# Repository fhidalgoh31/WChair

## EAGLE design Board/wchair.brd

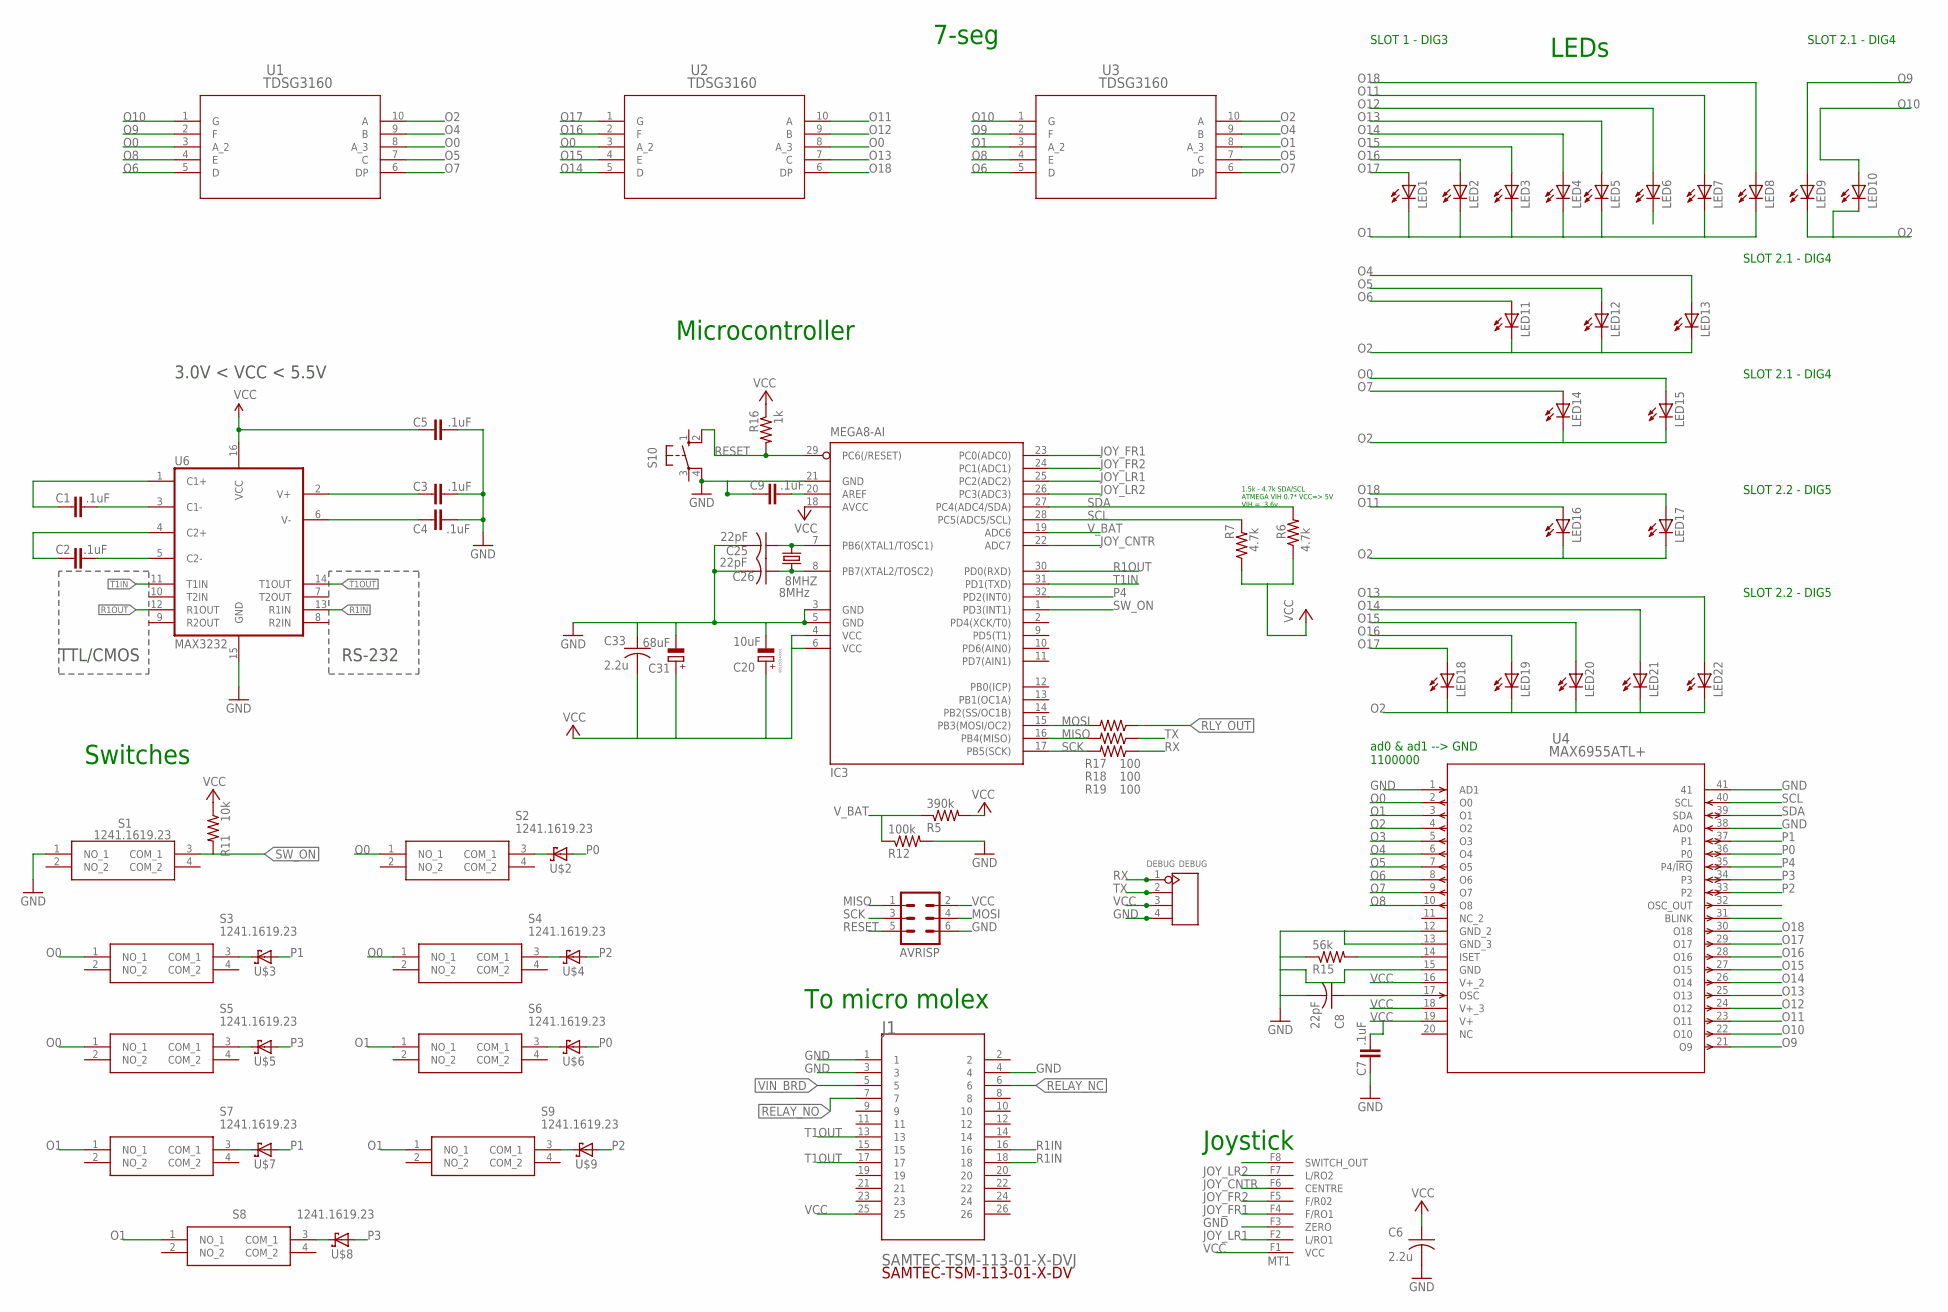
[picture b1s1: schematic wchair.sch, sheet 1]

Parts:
8MHZ: 8MHz; SM49; DIGIKEY 535-9089-1-ND
AVRISP: MA03-2; DIGIKEY ED10665-ND
C1, C2, C3, C4, C5, C7, C9: .1uF; 0603-CAP; DIGIKEY 399-15351-1-ND
C6, C33: 2.2u; C0603; DIGIKEY 1276-1183-1-ND
C8, C25, C26: 22pF; C0603; DIGIKEY 478-11384-1-ND
C20: 10uF; 153CLV-0405; DIGIKEY 493-2173-1-ND
C31: 68uF; 153CLV-0807; DIGIKEY PCE4412CT-ND‎
DEBUG: DEBUG; 4-PIN-HEADER; DIGIKEY 0
IC3: MEGA8-AI; TQFP32-08; DIGIKEY ATMEGA328P-AU-ND
J1: SAMTEC-TSM-113-01-X-DVJ; SAMTEC-TSM-113-01-X-DV
LED1, LED2, LED3, LED4, LED5, LED6, LED7, LED8, LED9, LED10, LED11, LED12, LED13, LED14, LED15, LED16, LED17, LED18, LED19, LED20, LED21, LED22: LEDCHIP-LED0805; CHIP-LED0805; DIGIKEY 1497-1434-1-ND
MT1: MINITEK2-8PINS
R5: 390k; R0603; DIGIKEY 311-390KGRCT-ND
R6, R7: 4.7k; R0603; DIGIKEY 311-4.7KGRCT-ND
R11: 10k; R0603; DIGIKEY RNCP0603FTD10K0CT-ND
R12: 100k; R0603; DIGIKEY RR08P100KDCT-ND
R15: 56k; R0603; DIGIKEY 749-1667-1-ND
R16: 1k; R0603; DIGIKEY RHM1.0KDCT-ND
R17, R18, R19: 100; R0603; DIGIKEY RR08P100DCT-ND
S1, S2, S3, S4, S5, S6, S7, S8, S9: 1241.1619.23; IP40-J-LEAD; DIGIKEY 486-1931-1-ND
S10: 10-XX; B3F-10XX; DIGIKEY SW400-ND
U1, U2, U3: TDSG3160; DIP10_TDS; DIGIKEY TDSG3160-M-ND
U4: MAX6955ATL+; 21-0141I_T4066-5
U6: MAX3232; SO16; DIGIKEY 296-14619-1-ND
U$2, U$3, U$4, U$5, U$6, U$7, U$8, U$9: SCHOTTKY; SOD-323

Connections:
C1+: C1.1, U6.1 (C1+)
C1-: C1.2, U6.3 (C1-)
C2+: C2.1, U6.4 (C2+)
C2-: C2.2, U6.5 (C2-)
GND: AVRISP.6, C3.2, C4.2, C5.2, C6.2, C7.1, C8.2, C9.1, C20.-, C25.2, C26.2, C31.-, C33.1, DEBUG.4, IC3.3 (GND), IC3.5 (GND), IC3.21 (GND), J1.1, J1.3, J1.4, MT1.F3 (ZERO), R12.2, R15.1, S1.1 (NO_1), S10.4 (P1), U4.1 (AD1), U4.12 (GND_2), U4.13 (GND_3), U4.15 (GND), U4.38 (AD0), U4.41, U6.15 (GND); also elsewhere on the board
JOY_CNTR: IC3.22 (ADC7), MT1.F6 (CENTRE)
JOY_FR1: IC3.23 (PC0(ADC0)), MT1.F4 (F/RO1)
JOY_FR2: IC3.24 (PC1(ADC1)), MT1.F5 (F/R02)
JOY_LR1: IC3.25 (PC2(ADC2)), MT1.F2 (L/RO1)
JOY_LR2: IC3.26 (PC3(ADC3)), MT1.F7 (L/RO2)
MISO: AVRISP.1, IC3.16 (PB4(MISO)), R18.2
MOSI: AVRISP.4, IC3.15 (PB3(MOSI/OC2)), R19.2
unnamed: S2.3 (COM_1), U$2.C
unnamed: S9.3 (COM_1), U$9.C
unnamed: S7.3 (COM_1), U$7.C
unnamed: S8.3 (COM_1), U$8.C
unnamed: S6.3 (COM_1), U$6.C
unnamed: S4.3 (COM_1), U$4.C
unnamed: S5.3 (COM_1), U$5.C
unnamed: S3.3 (COM_1), U$3.C
unnamed: R15.2, U4.14 (ISET)
unnamed: C8.1, U4.17 (OSC)
unnamed: 8MHZ.2, C25.1, IC3.7 (PB6(XTAL1/TOSC1))
unnamed: 8MHZ.1, C26.1, IC3.8 (PB7(XTAL2/TOSC2))
unnamed: C9.2, IC3.20 (AREF)
O0: LED15.A, S2.1 (NO_1), S3.1 (NO_1), S4.1 (NO_1), S5.1 (NO_1), U1.3 (A_2), U1.8 (A_3), U2.3 (A_2), U2.8 (A_3), U4.2 (O0)
O1: LED1.C, LED2.C, LED3.C, LED4.C, LED5.C, LED7.C, LED8.C, S6.1 (NO_1), S7.1 (NO_1), S8.1 (NO_1), S9.1 (NO_1), U3.3 (A_2), U3.8 (A_3), U4.3 (O1)
O2: LED9.C, LED10.C, LED11.C, LED12.C, LED13.C, LED14.C, LED15.C, LED16.C, LED17.C, LED18.C, LED19.C, LED20.C, LED21.C, LED22.C, U1.10 (A), U3.10 (A), U4.4 (O2)
O3: U4.5 (O3)
O4: LED13.A, U1.9 (B), U3.9 (B), U4.6 (O4)
O5: LED12.A, U1.7 (C), U3.7 (C), U4.7 (O5)
O6: LED11.A, U1.5 (D), U3.5 (D), U4.8 (O6)
O7: LED14.A, U1.6 (DP), U3.6 (DP), U4.9 (O7)
O8: U1.4 (E), U3.4 (E), U4.10 (O8)
O9: LED9.A, U1.2 (F), U3.2 (F), U4.21 (O9)
O10: LED10.A, U1.1 (G), U3.1 (G), U4.22 (O10)
O11: LED7.A, LED16.A, U2.10 (A), U4.23 (O11)
O12: LED6.A, U2.9 (B), U4.24 (O12)
O13: LED5.A, LED22.A, U2.7 (C), U4.25 (O13)
O14: LED4.A, LED21.A, U2.5 (D), U4.26 (O14)
O15: LED3.A, LED20.A, U2.4 (E), U4.27 (O15)
O16: LED2.A, LED19.A, U2.2 (F), U4.28 (O16)
O17: LED1.A, LED18.A, U2.1 (G), U4.29 (O17)
O18: LED8.A, LED17.A, U2.6 (DP), U4.30 (O18)
P0: U4.36 (P0), U$2.A, U$6.A
P1: U4.37 (P1), U$3.A, U$7.A
P2: U4.33 (P2), U$4.A, U$9.A
P3: U4.34 (P3), U$5.A, U$8.A
P4: IC3.32 (PD2(INT0)), U4.35 (P4/!IRQ)
R1IN: J1.16, J1.18, U6.13 (R1IN)
R1OUT: IC3.30 (PD0(RXD)), U6.12 (R1OUT)
RELAY_NC: J1.6; also elsewhere on the board
RELAY_NO: J1.7; also elsewhere on the board
RESET: AVRISP.5, IC3.29 (PC6(/RESET)), R16.2, S10.2 (S1)
RLY_OUT: R19.1; also elsewhere on the board
RX: DEBUG.1, R17.1
SCK: AVRISP.3, IC3.17 (PB5(SCK)), R17.2
SCL: IC3.28 (PC5(ADC5/SCL)), R7.2, U4.40 (SCL)
SDA: IC3.27 (PC4(ADC4/SDA)), R6.2, U4.39 (SDA)
SW_ON: IC3.1 (PD3(INT1)), R11.2, S1.3 (COM_1)
T1IN: IC3.31 (PD1(TXD)), U6.11 (T1IN)
T1OUT: J1.13, J1.17, U6.14 (T1OUT)
TX: DEBUG.2, R18.1
V+: C3.1, U6.2 (V+)
V-: C4.1, U6.6 (V-)
VCC: AVRISP.2, C5.1, C6.1, C7.2, C20.+, C31.+, C33.2, DEBUG.3, IC3.4 (VCC), IC3.6 (VCC), IC3.18 (AVCC), J1.25, MT1.F1 (VCC), R5.2, R6.1, R7.1, R11.1, R16.1, U4.16 (V+_2), U4.18 (V+_3), U4.19 (V+), U6.16 (VCC); also elsewhere on the board
VIN_BRD: J1.5; also elsewhere on the board
V_BAT: IC3.19 (ADC6), R5.1, R12.1

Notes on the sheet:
1.5k - 4.7k SDA/SCL ATMEGA VIH 0.7* VCC=> 5V VIH = 3.6v
Microcontroller
To micro molex
Joystick
Switches
7-seg
LEDs
RS-232
TTL/CMOS
3.0V < VCC < 5.5V
ad0 & ad1 --> GND 1100000
SLOT 1 - DIG3
SLOT 2.1 - DIG4
SLOT 2.2 - DIG5

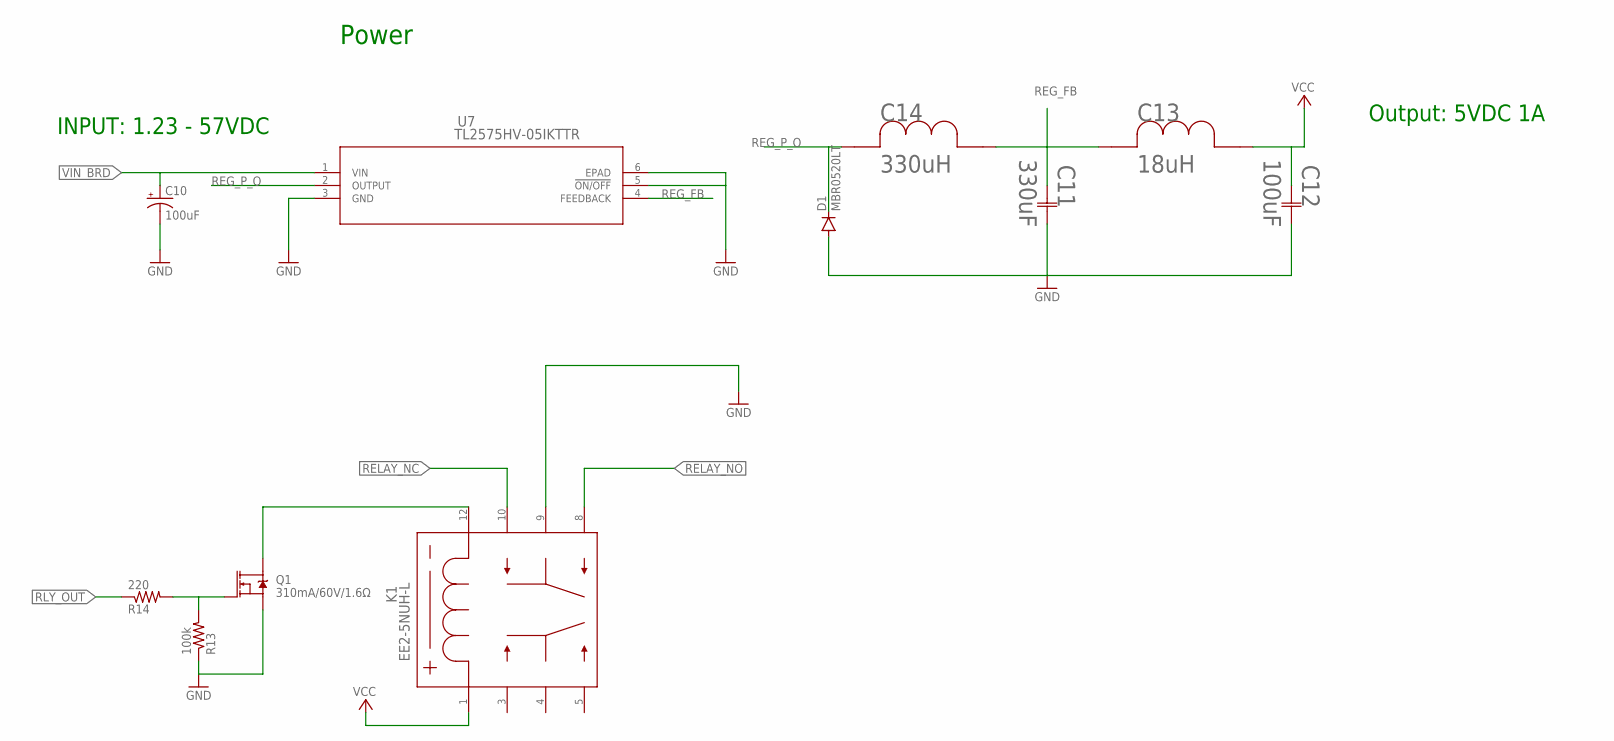
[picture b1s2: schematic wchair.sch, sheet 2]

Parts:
C10: 100uF; NIC_10X10.5_CAP; DIGIKEY PCE3942CT-ND
C11: 330uF; CAP_EEFK_D8; DIGIKEY PCE3768CT-ND
C12: 100uF; CAP_EEE_D; DIGIKEY PCE3852CT-ND
C13: 18uH; 18UH2.15A; DIGIKEY 732-4533-1-ND
C14: 330uH; 732-1698-1-ND; DIGIKEY 732-1698-1-ND
D1: MBR0520LT; SOD123; DIGIKEY MBR0520LCT-ND
K1: EE2-5NUH-L; EE2NUH; DIGIKEY 399-11016-1-ND‎
Q1: 310mA/60V/1.6Ω; SOT323; DIGIKEY SI2304BDS-T1-GE3CT-ND
R13: 100k; R0603; DIGIKEY RR08P100KDCT-ND
R14: 220; R0603; DIGIKEY A130087CT-ND
U7: TL2575HV-05IKTTR; KTT5_6P22X6P86; DIGIKEY 296-21833-1-ND

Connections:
GND: C10.-, C11.2, C12.2, D1.A, K1.9 (6), Q1.2 (S), R13.1, U7.3 (GND), U7.5 (!ON/OFF), U7.6 (EPAD); also elsewhere on the board
unnamed: Q1.1 (G), R13.2, R14.2
unnamed: K1.12 (8), Q1.3 (D)
REG_FB: C11.1, C13.1, C14.2, U7.4 (FEEDBACK)
REG_P_O: C14.1, D1.C, U7.2 (OUTPUT)
RELAY_NC: K1.10 (7); also elsewhere on the board
RELAY_NO: K1.8 (5); also elsewhere on the board
RLY_OUT: R14.1; also elsewhere on the board
VCC: C12.1, C13.2, K1.1; also elsewhere on the board
VIN_BRD: C10.+, U7.1 (VIN); also elsewhere on the board

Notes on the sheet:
Power
Output: 5VDC 1A
INPUT: 1.23 - 57VDC

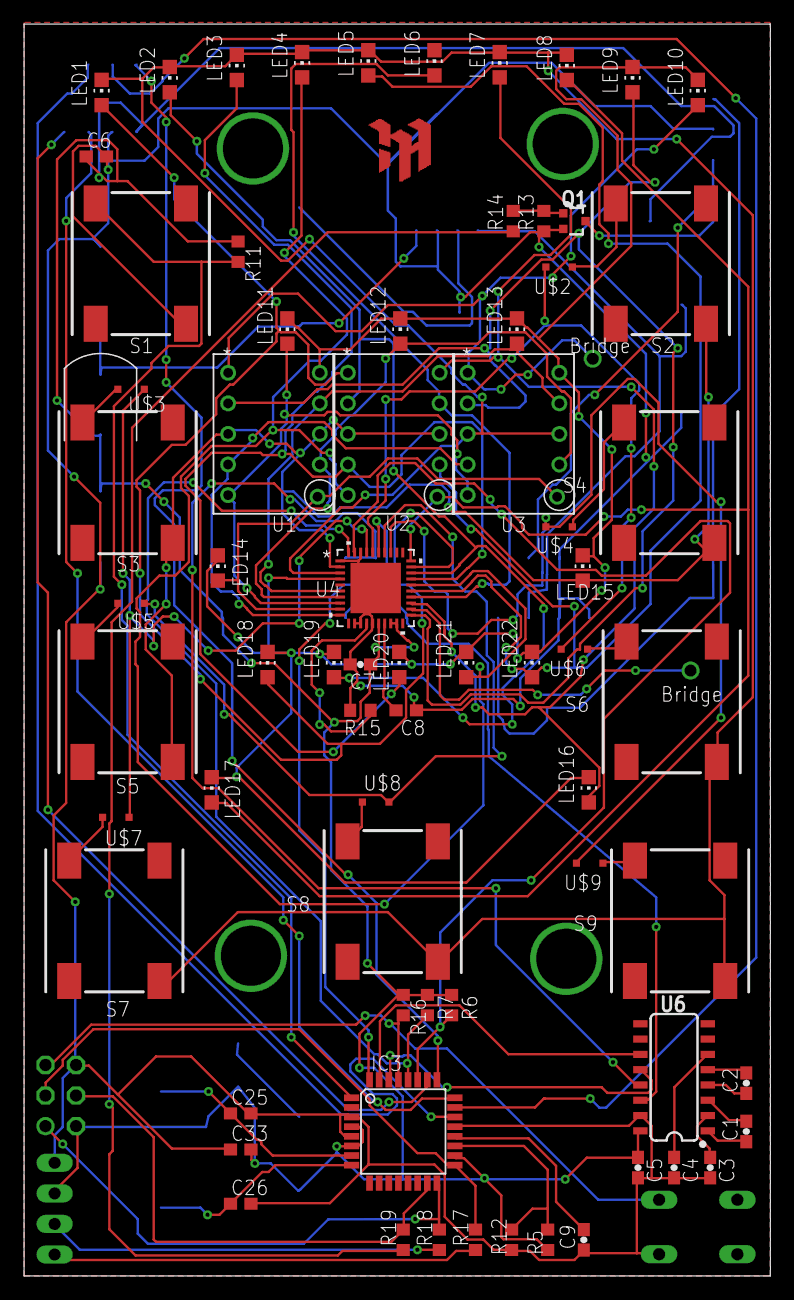
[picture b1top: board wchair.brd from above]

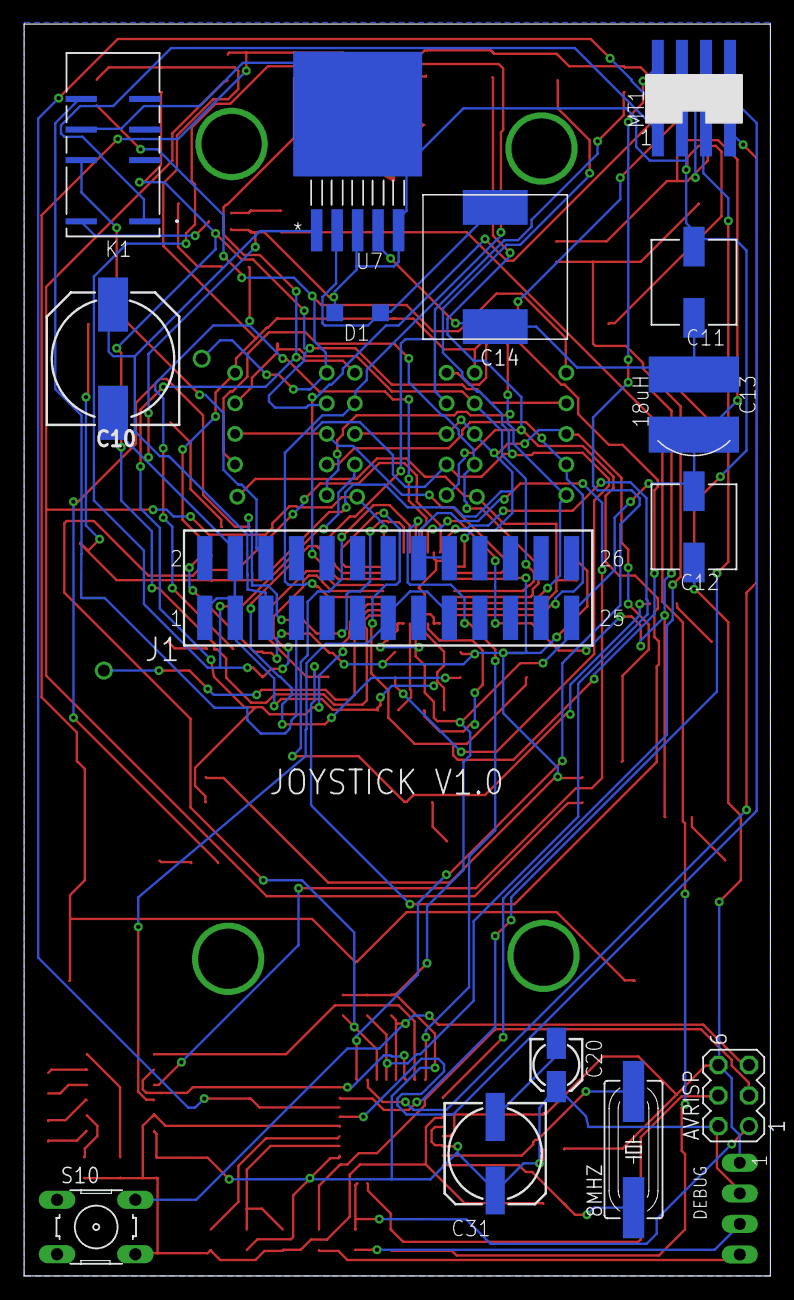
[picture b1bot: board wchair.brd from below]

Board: 2 copper layers, 62.0 x 104.0 mm, 86 parts (16 on the bottom side), 71 nets.

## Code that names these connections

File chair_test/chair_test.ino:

#include <SoftwareSerial.h>
#include <Wire.h>
#include "MAX6955.h"



#define JOY_FR1 A0
#define JOY_FR2 A1
#define JOY_LR1 A2
#define JOY_LR2 A3
#define JOY_CNTR A7

SoftwareSerial mySerial(13, 12); // RX, TX
MAX6955 leds(0B11000000);

void setup() {
  // set the data rate for the SoftwareSerial port
  Serial.begin(115200);
  mySerial.begin(115200);
 
  mySerial.println("Hello,  2??????");

 delay(10);
 leds.init();
 
}

void loop() { // run over and over
  
  // delay(2000);
  // Wire.beginTransmission(SLA_W(0B11000000));
  // leds.write(max6955_reg_digit3, 0x55); // no decode!
  
  // delay(2000);
  //  Wire.beginTransmission(SLA_W(0B11000000));
  // leds.write(max6955_reg_digit3, 0xAA); // no decode!

  
  delay(500);
}

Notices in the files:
parts and their libraries:
SparkFun-Capacitors: Licensing: Creative Commons ShareAlike 4.0 International - https://creativecommons.org/licenses/by-sa/4.0
